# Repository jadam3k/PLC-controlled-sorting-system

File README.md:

### Idk why journal doesnt work its not my fault
### i have all components for plc in my house so i dont have to buy new ones

# PLC-Controlled Sorting System

## Project Overview
This project is a small industrial-style **PLC-controlled item sorting system**. The system uses pneumatic cylinders, stepper motors, and a Siemens S7-1200 PLC to automatically sort objects based on rules. The design focuses on reliability, expandability, and realistic industrial while remaining suitable for educational purposes ;p.

Key features include:
- Pneumatic actuators for precise pushing of items
- Stepper motor-driven conveyors
- Siemens S7-1200 PLC for advanced control and future expansion
- Modular design with 2020 aluminum profiles
- Full BOM based on real, commercially available components

---
# BOM
| Item | Description | Quantity | Unit Price (PLN) | Total Price (PLN) | Total Price (USD) |
|---|---|---|---|---|---|
| Grove Ultrasonic Distance Sensor | Grove Ultrasonic Distance Sensor | 2 | 47 | 94 | 25.85 |
| 2020 aluminum profiles | 2020 aluminum profiles (6 m) | 1 | 340 | 340 | 93.47 |
| PU pneumatic hose | Polyurethane hose PU 8/5 mm | 1 | 4 | 4 | 1.10 |
| FRL filter | Drain-oil filter regulator FRL 1/4″ | 1 | 86 | 86 | 23.65 |
| Pneumatic solenoid valve NAMUR | NAMUR 5/2 G 1/4 230V AirTAC | 2 | 192 | 384 | 105.72 |
| Pneumatic cylinder | Pneumatic actuator 32×200 mm, double-acting | 1 | 310 | 310 | 85.22 |
| Stepper motor driver | Driver for NEMA 16/17/23/24 up to 5.6 A | 1 | 90 | 90 | 24.74 |
| Stepper motor NEMA23 | NEMA23 2 Nm, 3 A (57HS76-3004A08) | 1 | 118 | 118 | 32.45 |
| DIN rail power supply | 24 V 15 W Qoltec DIN-rail | 1 | 49 | 49 | 13.47 |
| Circuit breaker | Overcurrent breaker HN-C20/1 | 1 | 23 | 23 | 6.32 |
| Control button | ONPOW LAS0-B3Y-11/R red NO/NC | 2 | 20 | 40 | 10.99 |
| **Total** |  |  |  | **1,938 PLN** | **≈ 534 USD** |

---

## Project Stages
1. **CAD Modeling** – Designed full 3D assembly of the conveyor and actuator system.
2. **PLC Programming** – Ladder Diagram code implemented in CODESYS for controlling cylinders and motors.
3. **BOM Creation** – Selected all components to ensure reliability and expandability.
4. **Controller Upgrade** – Replaced Siemens LOGO! with Siemens S7-1200 for professional-grade PLC control.
5. **Testing & Verification** – Checked calculations, motor/actuator sizing, and system stability in simulation.
6. **Pneumatic System Setup** – Assembled cylinders, valves, FRL, tubing, and fittings.
7. **Sorting Area Design** – Configured sliding area for sorted items with correct actuator positioning.
8. **Optimizations** – Improved pulley design, code reliability, and 3D structure aesthetics.

---

## 3D Model / Schematic

---

## LD CODE

## PLC SCHEMATIC AND view

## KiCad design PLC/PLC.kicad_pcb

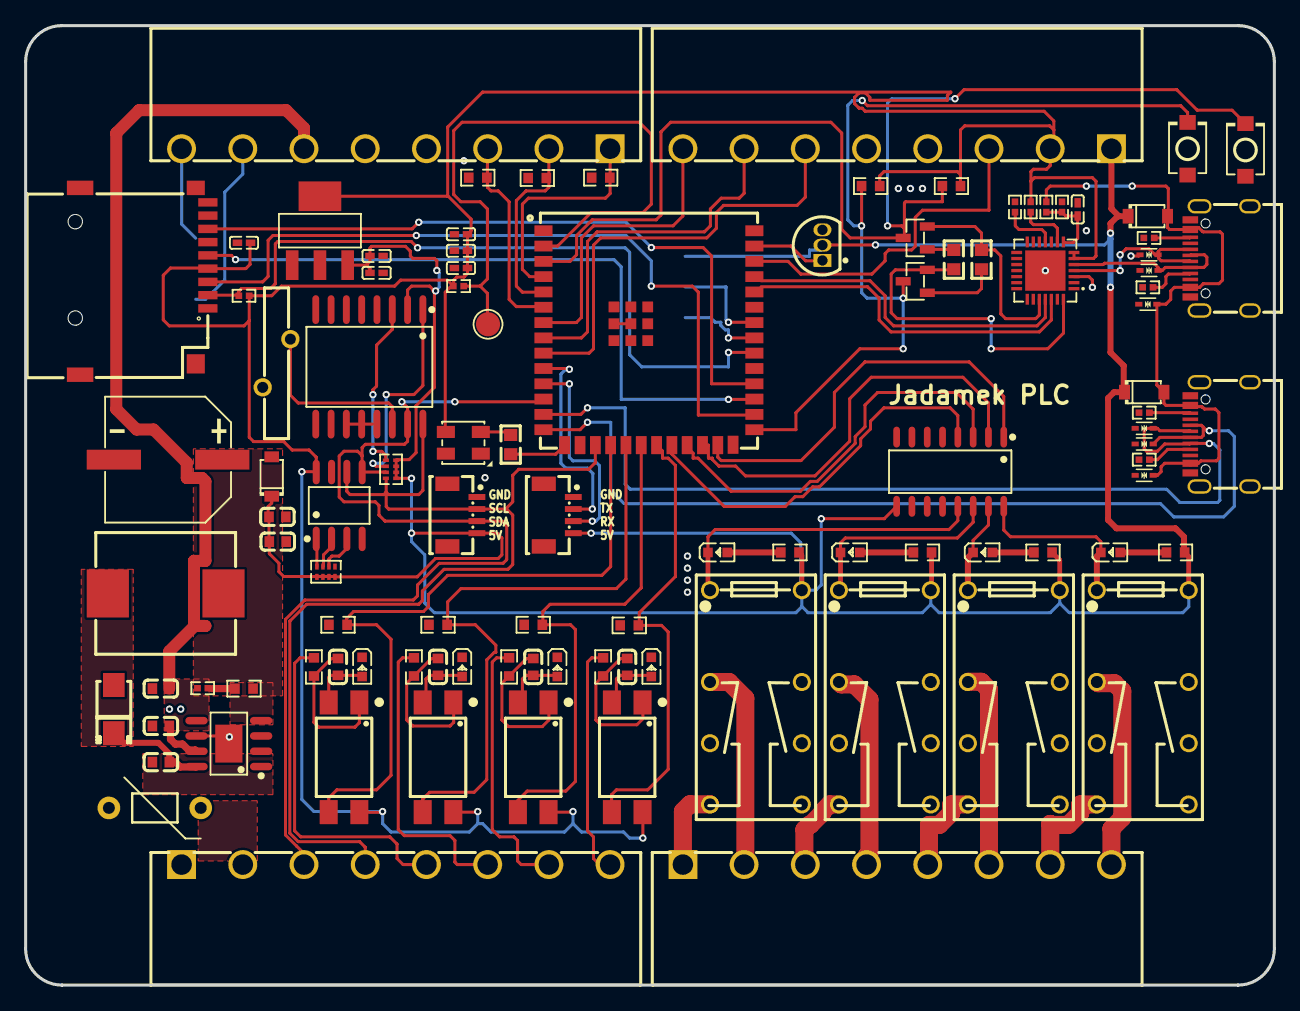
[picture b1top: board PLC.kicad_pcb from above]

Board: 2 copper layers, 103.6 x 79.6 mm, 104 parts (1 on the bottom side), 93 nets.

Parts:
1: MOV
BOOT: SW-SMD_L3.9-W3.0-P4.45
C1, C2, C3, C4, C16, C18, C19, C20, C21: C0603
C17: CAP-SMD_BD10.0-L10.3-W10.3-LS11.3-FD
C22, C23, C24, C25, C26, C27, C28: C0402
CARD1: TF-SMD_TF-PUSH
CN1, CN5, CN6, CN7: CONN-TH_8P-P5.08_HT508R-5.08-8P
D11, D22, D23: SOD-123_L2.7-W1.6-LS3.7-RD
D21: SMA_L4.2-W2.7-LS5.0-RD
ESP_3V3: TP-SMD
K5, K6, K7, K8: RELAY-TH_HRS2H-S-XX
LED1, LED2, LED3, LED4, LED5, LED6, LED7, LED8: LED0603-RD
Q1, Q2: SOT-23-3_L2.9-W1.3-P1.90-LS2.4-BR
R1, R2, R3, R4, R5, R6, R7, R8, R9, R10, R11, R12, R13, R16, R47, R60, R62, R63, R64, R65, R66: R0603
R49, R50, R51, R52, R53, R54, R55, R56, R57, R58, R59: R0402
RN1, RN2: RES-ARRAY-SMD_0402-8P-L2.0-W1.0-BL
RST: SW-SMD_L3.9-W3.0-P4.45
U1: SOP-16_L10.2-W3.9-P1.27-LS6.0-BL
U2, U3, U4, U5: SMD-4_L6.5-W4.6-P2.54-LS10.0-TL
U6: SOIC-16_L10.3-W7.5-P1.27-LS10.3-BL
U14: SMD-7_L42.8-W15.2-P2.54_TTL485
U27: ESOP-8_L4.9-W3.9-P1.27-LS6.0-BL-EP-2
U28: IND-SMD_L11.6-W10.1
U29: WIRELM-SMD_ESP32-S3-WROOM-1U
U30: QFN-28_L5.0-W5.0-P0.50-TL-EP3.3
U31, U32, U33, U34, U35, U36: SOD-523_L1.2-W0.8-LS1.6-BI
U37: SOIC-8_L4.9-W3.9-P1.27-LS6.0-BL
U38: BAT-TH_CR1220ZTV02-4
U39, U40: CONN-SMD_4P-P1.00_ZX-SH1.0-4PLN
U41: LED-SMD_4P-L3.5-W3.5-BR_SK6812MINI-HS
U42: TO-92-3_L4.8-W3.7-P1.27-L
U43: SOT-223_L6.5-W3.5-P2.30-LS7.0-BR
USBC1, USBC2: USB-C_SMD-TYPE-C-31-M-12

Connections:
32K: RN2.3, U6.1
$3N428: LED1.2, R1.1
$3N1598: LED2.2, R2.1
$3N1805: LED3.2, R3.1
$3N2012: LED4.2, R4.1
$3N2519: C1.1, LED5.2, U2.2
$3N2521: C1.2, R5.2, U2.1
$3N2913: C2.1, LED6.2, U3.2
$3N2918: C2.2, R7.2, U3.1
$3N3423: C3.1, LED7.2, U4.2
$3N3428: C3.2, R9.2, U4.1
$3N3442: C4.1, LED8.2, U5.2
$3N3447: C4.2, R11.2, U5.1
$3N6977: C16.1, U27.1
$3N6978: C16.2, D21.1, U27.8, U28.1
$3N6979: C17.1, D11.2, R47.2, U28.2
$3N6980: R47.1, R59.2, U27.4
$3N11544: R53.2, U30.9
$3N11546: R54.2, U30.11
$3N11552: C23.2, R55.2, R56.2, U30.8
$3N11749: ESP_3V3.1, R57.2, U29.2
$3N15033: RN1.6, U37.2
$3N15178: U6.14, U38.1
$3N15314: RN1.7, U37.3
$3N15320: RN1.5, U37.1
$3N16978: Q1.1, R60.1
$3N16979: Q2.1, R13.1
%IW0.0: CN6.1, R64.2, U29.4
%IW0.1: CN6.2, R63.1, U29.5
%IW0.2: CN6.3, R62.1, U29.6
%IX0.0: R6.1, U2.3, U29.21
%IX0.1: R8.1, U3.3, U29.20
%IX0.2: R10.1, U4.3, U29.19
%IX0.3: R12.1, U5.3, U29.18
%QX0.0: U1.1, U29.25
%QX0.1: U1.2, U29.24
%QX0.2: U1.3, U29.23
%QX0.3: U1.4, U29.22
+5V: C20.2, C21.2, C27.2, C28.2, CN5.1, D11.1, D22.1, D23.1, K5.2, K6.2, K7.2, K8.2, R1.2, R2.2, R3.2, R4.2, RN1.1, RN1.2, RN1.3, RN1.4, RN2.5, RN2.6, RN2.7, RN2.8, U1.9, U6.2, U14.1, U39.4, U40.4, U42.2, U43.3
A485: CN6.8, U14.7
B485: CN6.7, U14.6
CC1: R50.1, USBC1.A5
CC2: R49.1, USBC1.B5
CC3: R52.1, USBC2.A5
CC4: R51.1, USBC2.B5
CHIP_PU: Q1.3, R66.1, RST.2, U29.3
CS: CARD1.2, R58.2, U29.32
DTR: Q2.2, R60.2, U30.28
GND: 1.P$1, BOOT.1, C17.2, C18.1, C19.1, C20.1, C21.1, C22.1, C23.1, C24.1, C25.1, C26.1, C27.1, C28.1, CARD1.6, CARD1.10, CARD1.11, CARD1.12, CARD1.13, CN5.4, CN5.5, CN6.4, CN6.5, CN7.1, D21.2, LED5.1, LED6.1, LED7.1, LED8.1, R6.2, R8.2, R10.2, R12.2, R49.2, R50.2, R51.2, R52.2, R54.1, R56.1, R59.1, R62.2, R63.2, R64.1, RST.1, U1.8, U6.5, U6.6, U6.7, U6.8, U6.9, U6.10, U6.11, U6.12, U6.13, U14.4, U27.6, U27.9, U29.1, U29.40, U29.41, U30.3, U30.29, U31.1, U32.1, U33.1, U34.1, U35.1, U36.1, U37.4, U38.2, U39.1, U39.5, U39.6, U40.1, U40.5, U40.6, U41.1, U42.3, U43.1, USBC1.A1, USBC1.A12, USBC1.B1, USBC1.B12, USBC2.A1, USBC2.A12, USBC2.B1, USBC2.B12
GPIO0: BOOT.2, Q2.3, R65.1, U29.27
GPIO1: U29.39, U42.1
GPIO2: CN5.3, U29.38
GPIO3: R16.1, U29.15
GPIO7: CN5.8, U29.7
GPIO15: CN5.7, U29.8
GPIO16: CN5.6, U29.9
GPIO19: U29.13, U35.2, USBC2.A7, USBC2.B7
GPIO20: U29.14, U36.2, USBC2.A6, USBC2.B6
MISO: CARD1.7, U29.30
MOSI: CARD1.3, U29.28
OUT1: CN7.8, R5.1
OUT2: CN7.7, R7.1
OUT3: CN7.6, R9.1
OUT4: CN7.5, R11.1
RGB_CTRL: R16.2, U41.2
RLY1: K5.1, LED1.1, U1.16
RLY1A: CN1.8, K5.3
RLY1B: CN1.7, K5.5
RLY2: K6.1, LED2.1, U1.15
RLY2A: CN1.6, K6.3
RLY2B: CN1.5, K6.5
RLY3: K7.1, LED3.1, U1.14
RLY3A: CN1.4, K7.3
RLY3B: CN1.3, K7.5
RLY4: K8.1, LED4.1, U1.13
RLY4A: CN1.2, K8.3
RLY4B: CN1.1, K8.5
RTS: Q1.2, R13.2, U30.24
RX2: U29.11, U39.3
RX485: U14.2, U29.34
SCK: CARD1.5, U29.29
SCL: CN7.4, RN2.1, U6.16, U29.17, U37.6, U40.2
SDA: CN7.3, RN2.2, U6.15, U29.12, U37.5, U40.3
SQW: RN2.4, U6.3
TX2: U29.10, U39.2
TX485: U14.3, U29.33
U0RXD: U29.36, U30.26
U0TXD: U29.37, U30.25
USB_DN: U30.5, U32.2, USBC1.A7, USBC1.B7
USB_DP: U30.4, U33.2, USBC1.A6, USBC1.B6
VBUS: D22.2, D23.2, R55.1, U31.2, U34.2, USBC1.A4, USBC1.A9, USBC1.B4, USBC1.B9, USBC2.A4, USBC2.A9, USBC2.B4, USBC2.B9
VCC: C22.2, C24.2, C25.2, C26.2, CARD1.4, CN5.2, R53.1, R57.1, R58.1, R65.2, R66.2, U2.4, U3.4, U4.4, U5.4, U30.6, U30.7, U37.8, U41.3, U43.2, U43.4
VIN: 1.P$2, C18.2, C19.2, CN6.6, CN7.2, U27.5, U27.7

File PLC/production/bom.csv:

Designator,Footprint,Quantity,Value,LCSC Part #
1,MOV,1,,
"BOOT, RST",SW-SMD_L3.9-W3.0-P4.45,2,,
"C1, C16, C18, C19, C2, C20, C21, C3, C4",C0603,9,,
C17,CAP-SMD_BD10.0-L10.3-W10.3-LS11.3-FD,1,,
"C22, C23, C24, C25, C26, C27, C28",C0402,7,,
CARD1,TF-SMD_TF-PUSH,1,,
"CN1, CN5, CN6, CN7",CONN-TH_8P-P5.08_HT508R-5.08-8P,4,,
"D11, D22, D23",SOD-123_L2.7-W1.6-LS3.7-RD,3,,
D21,SMA_L4.2-W2.7-LS5.0-RD,1,,
ESP_3V3,TP-SMD,1,,
"K5, K6, K7, K8",RELAY-TH_HRS2H-S-XX,4,,
"LED1, LED2, LED3, LED4, LED5, LED6, LED7, LED8",LED0603-RD,8,,
"Q1, Q2",SOT-23-3_L2.9-W1.3-P1.90-LS2.4-BR,2,,
"R1, R10, R11, R12, R13, R16, R2, R3, R4, R47, R5, R6, R60, R62, R63, R64, R65, R66, R7, R8, R9",R0603,21,,
"R49, R50, R51, R52, R53, R54, R55, R56, R57, R58, R59",R0402,11,,
"RN1, RN2",RES-ARRAY-SMD_0402-8P-L2.0-W1.0-BL,2,,
U1,SOP-16_L10.2-W3.9-P1.27-LS6.0-BL,1,,
U14,SMD-7_L42.8-W15.2-P2.54_TTL485,1,,
"U2, U3, U4, U5",SMD-4_L6.5-W4.6-P2.54-LS10.0-TL,4,,
U27,ESOP-8_L4.9-W3.9-P1.27-LS6.0-BL-EP-2,1,,
U28,IND-SMD_L11.6-W10.1,1,,
U29,WIRELM-SMD_ESP32-S3-WROOM-1U,1,,
U30,QFN-28_L5.0-W5.0-P0.50-TL-EP3.3,1,,
"U31, U32, U33, U34, U35, U36",SOD-523_L1.2-W0.8-LS1.6-BI,6,,
U37,SOIC-8_L4.9-W3.9-P1.27-LS6.0-BL,1,,
U38,BAT-TH_CR1220ZTV02-4,1,,
"U39, U40",CONN-SMD_4P-P1.00_ZX-SH1.0-4PLN,2,,
U41,LED-SMD_4P-L3.5-W3.5-BR_SK6812MINI-HS,1,,
U42,TO-92-3_L4.8-W3.7-P1.27-L,1,,
U43,SOT-223_L6.5-W3.5-P2.30-LS7.0-BR,1,,
U6,SOIC-16_L10.3-W7.5-P1.27-LS10.3-BL,1,,
"USBC1, USBC2",USB-C_SMD-TYPE-C-31-M-12,2,,

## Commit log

2025-11-19 final
2025-11-19 Track .stp files using Git LFS
2025-11-19 Adjust price for aluminum extrusion profiles
    Updated the price of aluminum extrusion profiles in the bill of materials.
2025-11-19 Change price of 2020 aluminum profiles
    Updated the price of 2020 aluminum profiles from 300.00 to 340.00.
2025-11-19 Fix unit notation and update total price in bom.csv
2025-11-19 Update README with journal issue note
    Added a note about journal issues in the README.
2025-11-19 Revise Bill of Materials format and values
    Updated the Bill of Materials section with a new format and corrected quantities and prices.
2025-11-19 Convert BOM list to markdown table format
    Formatted the bill of materials into a table for better readability.
2025-11-20 Revise BOM section with detailed pricing
    Updated the Bill of Materials (BOM) section with detailed itemized costs and removed the previous BOM format.
2025-11-20 Add PLC schematic images to README
2025-11-20 Add initial component list to plcbom.csv
2025-11-20 Update plcbom.csv with additional components
